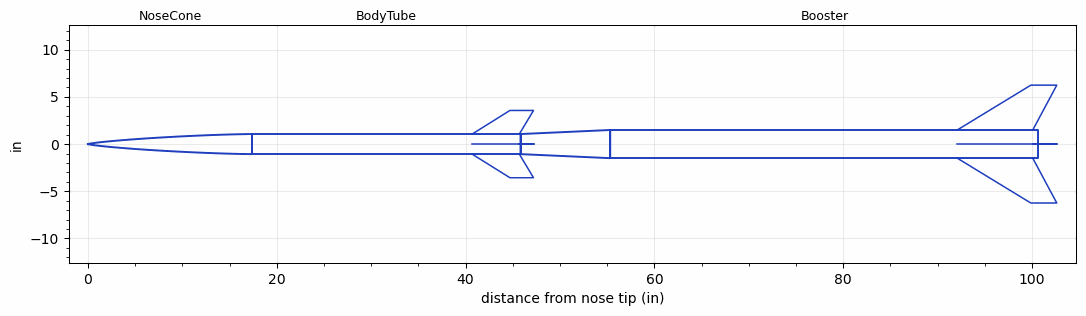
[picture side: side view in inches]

<RASAeroDocument>
 <FileVersion>2</FileVersion>
 <RocketDesign>
  <NoseCone>
   <Length>17.375</Length>
   <Diameter>2.125</Diameter>
   <Shape>Von Karman Ogive</Shape>
   <Location>0</Location>
  </NoseCone>
  <BodyTube>
   <Length>28.443</Length>
   <Diameter>2.125</Diameter>
   <Location>17.375</Location>
   <Fin>
    <Count>4</Count>
    <Chord>5</Chord>
    <Span>2.5</Span>
    <SweepDistance>4</SweepDistance>
    <TipChord>2.5</TipChord>
    <Thickness>0.125</Thickness>
    <LERadius>0.01</LERadius>
    <Location>5.125</Location>
    <AirfoilSection>Hexagonal</AirfoilSection>
    <FX1>1</FX1>
    <FX3>1</FX3>
   </Fin>
  </BodyTube>
  <Booster>
   <Length>45.366</Length>
   <Diameter>2.985</Diameter>
   <InsideDiameter>2.125</InsideDiameter>
   <Location>45.818</Location>
   <ShoulderLength>9.5</ShoulderLength>
   <Fin>
    <Count>4</Count>
    <Chord>8</Chord>
    <Span>4.75</Span>
    <SweepDistance>7.794</SweepDistance>
    <TipChord>2.75</TipChord>
    <Thickness>0.18</Thickness>
    <LERadius>0.01</LERadius>
    <Location>8.6</Location>
    <AirfoilSection>Hexagonal</AirfoilSection>
    <FX1>1</FX1>
    <FX3>1</FX3>
   </Fin>
  </Booster>
  <Surface>Rough Camouflage Paint</Surface>
  <ModifiedBarrowman>True</ModifiedBarrowman>
  <Turbulence>True</Turbulence>
  <UseBooster1>False</UseBooster1>
  <UseBooster2>False</UseBooster2>
 </RocketDesign>
 <LaunchSite>
  <Altitude>1344</Altitude>
  <Pressure>30.05</Pressure>
  <RodAngle>0</RodAngle>
  <RodLength>10</RodLength>
  <Temperature>63.76</Temperature>
  <WindSpeed>0</WindSpeed>
 </LaunchSite>
 <Recovery>
  <Altitude1>1000</Altitude1>
  <Altitude2>1500</Altitude2>
  <DeviceType1>Parachute</DeviceType1>
  <DeviceType2>Parachute</DeviceType2>
  <Event1>True</Event1>
  <Event2>True</Event2>
  <Size1>9</Size1>
  <Size2>36</Size2>
  <EventType1>Apogee</EventType1>
  <EventType2>Altitude</EventType2>
  <CD1>0.8</CD1>
  <CD2>0.8</CD2>
 </Recovery>
 <SimulationList>
  <Simulation>
   <SustainerEngine>K2144  (SRT)</SustainerEngine>
   <SustainerLaunchWt>5.94</SustainerLaunchWt>
   <SustainerNozzleDiameter>2.125</SustainerNozzleDiameter>
   <SustainerCG>30.39</SustainerCG>
   <SustainerIgnitionDelay>0.5</SustainerIgnitionDelay>
   <Booster1Engine>M3464LB  (Loki)</Booster1Engine>
   <Booster1LaunchWt>25.2</Booster1LaunchWt>
   <Booster1SeparationDelay>0</Booster1SeparationDelay>
   <Booster1IgnitionDelay>0</Booster1IgnitionDelay>
   <Booster1CG>67.82</Booster1CG>
   <Booster1NozzleDiameter>1.818</Booster1NozzleDiameter>
   <IncludeBooster1>True</IncludeBooster1>
   <Booster2Delay>0</Booster2Delay>
   <IncludeBooster2>False</IncludeBooster2>
   <TimetoApogee>39.90981</TimetoApogee>
   <MaxAltitude>41775.18</MaxAltitude>
   <MaxVelocity>4116.501</MaxVelocity>
  </Simulation>
 </SimulationList>
</RASAeroDocument>
